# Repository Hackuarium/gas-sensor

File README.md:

# gas-sensor

The goal is to create a box allowing the determination of the gas composition of a bioreactor. The sensor that will be available are: CO2 (MH-Z19), H2 (MQ-8) and methane (MQ-4) as well as temperature (DS18B20) and humidity (DHT-22).

The board will be compatible with arduino Lilapad Pro using a dedicated PCB.

Need to compensate for humidity and temperature ???

- https://forum.arduino.cc/index.php?topic=433045.0

## Cloning the project

This project uses SUBMODULES

In order to clone use:

`git clone --recurse-submodules https://github.com/hackuarium/gas-sensor`

To update the submodules

`git submodule update --recursive --remote`

## Sensors

| name_pin | function    | model   |                             | Arduino library                                |
| -------- | ----------- | ------- | --------------------------- | ---------------------------------------------- |
| CH4      | CH4         | MQ-4    |                             |                                                |
| H2       | H2          | MQ-8    |                             |                                                |
| CO2      | CO2         | MH-Z19  | 3.3v (for RX / TX) + 5v!!!! | https://github.com/crisap94/MHZ19              |
| TEMP     | temperature | DS18B20 |                             |                                                |
| HUM      | humidity    | DHT-22  |                             | https://github.com/adafruit/DHT-sensor-library |

Gaz sensor: http://www.china-total.com/Product/meter/gas-sensor/Gas-sensor.htm

Gaz sensor on sparkfun:
https://www.sparkfun.com/products/8891
https://www.sparkfun.com/products/9404

Gaz sensor on mysensors: https://www.mysensors.org/build/gas

Drying the air / pumping
Particulate or Coalescing Filters
http://www.pneumaticplus.com/pneumaticplus-saf4000-series-particulate-air-filter-1-2-npt-with-bracket/
https://www.aliexpress.com/item/15L-M-12V-dc-electric-diaphragm-brush-small-air-compressor-pump/1790013118.html

Fans

https://www.pelonistechnologies.com/micro-fans

Pneumatic
https://www.alibaba.com/product-detail/A102-China-sup

## Pinout

| n° Arduino | port | pin      |                  |     |
| ---------- | ---- | -------- | ---------------- | --- |
| A0         | PC0  | A0       | H2               |     |
| A1         | PC1  | A1       | H2_ON            |     |
| A2         | PC2  | A2       | CO2_RX           |     |
| A3         | PC3  | A3       | CO2_TX           |     |
| A4         | PC4  | SDA      | Slave I2C        |     |
| A5         | PC5  | SCL      | Slave I2C        |     |
| A6         | ADC6 | A6       | CH4              |     |
| A7         | ADC7 | A7       | CH4_ON           |     |
| 0          | PD0  | RX       | FTDI             |     |
| 1          | PD1  | TX       | FTDI             |     |
| 2          | PD2  | D2       | /                |     |
| 3          | PD3  | D3       | PWM_MH-Z19       | PWM |
| 4          | PD4  | D4       | TEMPERATURE      |     |
| 5          | PD5  | D5       | HUMIDITY         | PWM |
| 6          | PD6  | D6       | LCD RS           | PWM |
| 7          | PD7  | D7       | /                |     |
| 8          | PB0  | D8       | LCD E            |     |
| 9          | PB1  | D9       | LCD LED          | PWM |
| 10         | PB2  | D10      | LCD1             | PWM |
| 11         | PB3  | MOSI D11 | LCD2             | PWM | mh |
| 12         | PB4  | MISO D12 | LCD3             |     |
| 13         | PB5  | SCK D13  | LCD4             |     |

n.b: Two pins (PD2 and PD7) are free and could be used to add a fourth sensor.

## Power supply

- plug for 5V
- MCP1703-33 for µC power supply

## Schematic
Here is the schematic of the main components of the project:

ATMega328P:

Sensors:

Others (LCD, crystal and voltage regulator):

## List of components
| Type           | Value | Quantity | Footprint                   |
|----------------|-------|----------|-----------------------------|
| Resistor       | 1M    | 1        | 0805 Handsolder             |
| Resistor       | 10k   | 2        | 0805 Handsolder             |
| Resistor       | 4.7k  | 2        | 0805 Handsolder             |
| Resistor       | 4.7   | 1        | 0805 Handsolder             |
| Potentiometer  |       | 1        | TRIM_3362R-1-222            |
| Capacitor      | 10µF  | 2        | 0805 Handsolder             |
| Capacitor      | 100nF | 3        | 0805 Handsolder             |
| Capacitor      | 18pF  | 2        | 0805 Handsolder             |
| Diode Shottky  |       | 3        | D_SOD-123                   |
| BSP75          |       | 2        | SOT-223-3_TabPin3           |
| Crystal        | 8Mhz  | 1        | Crystal_SMD_5032 Handsolder |
| MCP-1703A      |       | 1        | SOT-23                      |
| ATMega328P-AU  |       | 1        | TQFP-32_7x7mm_P0.8mm        |
| 5V power source|       | 1        | BarrelJack_Horizontal       |
| RJ12           |       | 1        | RJ12_Amphenol_54601         |
| LCD Screen     |       | 1        | WC1602A                     |
| MHZ-19 (CO2)   |       | 1        | footprints: MHZ-19          |
| MQ-4 (CH4)     |       | 1        | footprints: MQ-4            |
| MQ-8 (H2)      |       | 1        | footprints: MQ-8            |
| DHT22 (Hum)    |       | 1        | footprints: DHT-22_HOR      |
| DS18B20 (Temp) |       | 1        | TO-92_Inline                |

## Inspiration for PCB

* https://github.com/Hackuarium/esp-12e/tree/master/kicad

  - ICSP - TAG connect - take care of pin mapping !
  - RJ12 - 6P6C
  - FTDI232
  - LCD: WC1602A

## Get inspired from scale board

- https://github.com/Hackuarium/beemos/tree/master/scale-i2c/eagle
- https://github.com/Hackuarium/esp-12e/tree/master/kicad/libs

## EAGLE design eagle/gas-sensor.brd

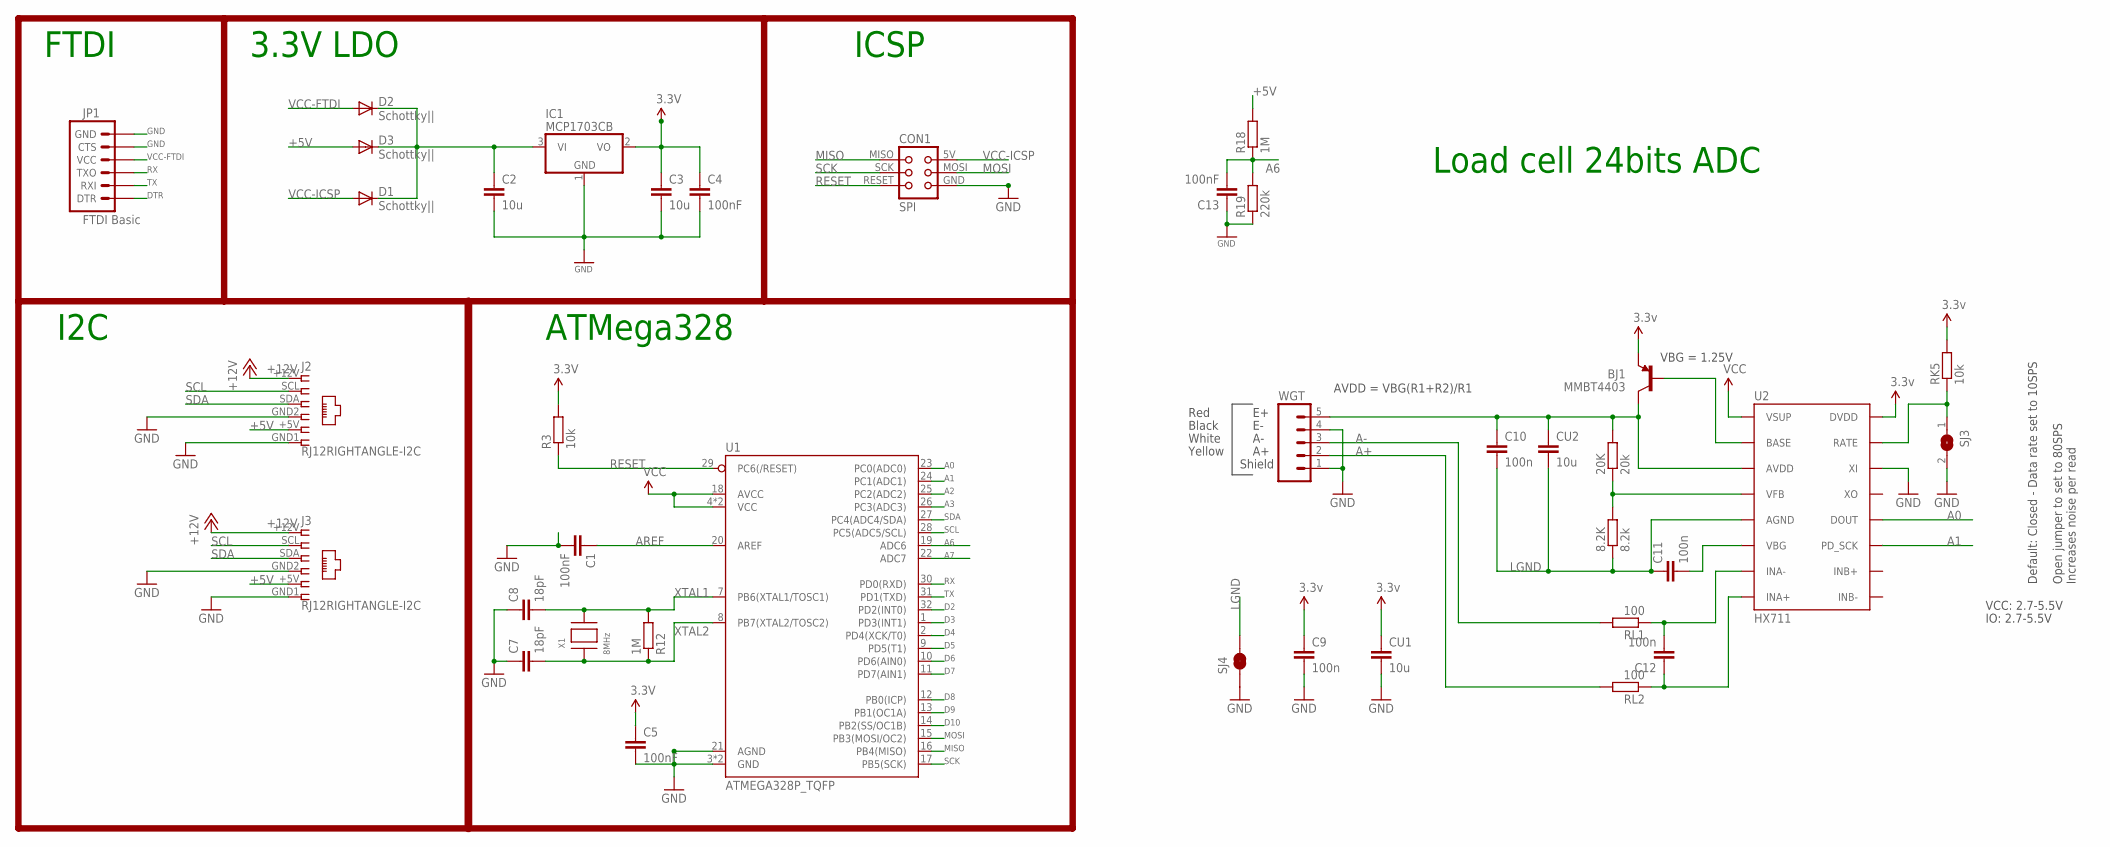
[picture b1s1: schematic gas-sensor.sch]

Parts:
8.2K: 8.2k; M0805
20K: 20k; M0805
BJ1: MMBT4403; SOT23-3
C1, C4, C5, C13: 100nF; C0805K; MPN 80-C1206C104K5R; LCSC C49678
C2, C3: 10u; C0805K; MPN 77-VJ1206V106ZXQTBC; LCSC C15850
C7, C8: 18pF; C0805K; MPN 77-VJ1206A180JXXPBC; LCSC C1797
C9, C10, C11, C12: 100n; C0805
CON1: SPI; TC2030-MCP
CU1, CU2: 10u; C0805
D1, D2, D3: Schottky||; SOD123; MPN 621-1N5819HW-F; LCSC C82544
IC1: MCP1703CB; SOT23; LCSC C53352
J2, J3: RJ12RIGHTANGLE-I2C; RJ12-RIGHTANGLE-I2C
JP1: FTDI Basic; 1X06
R3: 10k; R0805; LCSC C17513
R12, R18: 1M; R0805; LCSC C17514
R19: 220k; R0805; LCSC C17514
RK5: 10k; M0805
RL1, RL2: 100; M0805
SJ3: SJ
SJ4: JUMPER-PAD-2-NC_BY_TRACE; PAD-JUMPER-2-NC_BY_TRACE_YES_SILK
U1: ATMEGA328P_TQFP; TQFP32-08
U2: HX711; SO16
WGT: M05PTH; 1X05
X1: 8MHz; NX6035; MPN 729-F60800010; LCSC C122522

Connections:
3.3V: BJ1.2 (E), C3.1, C4.1, C5.1, C9.1, CU1.1, IC1.2 (VO), R3.2, RK5.2, U1.4 (VCC), U1.6 (VCC), U1.18 (AVCC), U2.1 (VSUP), U2.16 (DVDD)
+5V: D3.A, J2.+5V (5), J3.+5V (5), R18.2
+12V: J2.+12V (1), J3.+12V (1)
+XV: C2.1, D1.C, D2.C, D3.C, IC1.3 (VI)
A0: U1.23 (PC0(ADC0)), U2.12 (DOUT)
A1: U1.24 (PC1(ADC1)), U2.11 (PD_SCK)
A2: U1.25 (PC2(ADC2))
A3: U1.26 (PC3(ADC3))
A6: C13.2, R18.1, R19.2, U1.19 (ADC6)
A7: U1.22 (ADC7)
A+: RL2.2, WGT.2
A-: RL1.2, WGT.3
AREF: C1.1, U1.20 (AREF)
CN3: C11.2, U2.6 (VBG)
D2: U1.32 (PD2(INT0))
D3: U1.1 (PD3(INT1))
D4: U1.2 (PD4(XCK/T0))
D5: U1.9 (PD5(T1))
D6: U1.10 (PD6(AIN0))
D7: U1.11 (PD7(AIN1))
D8: U1.12 (PB0(ICP))
D9: U1.13 (PB1(OC1A))
D10: U1.14 (PB2(SS/OC1B))
DTR: JP1.1 (DTR)
GND: C1.2, C2.2, C3.2, C4.2, C5.2, C7.1, C8.1, C9.2, C13.1, CON1.GND, CU1.2, IC1.1 (GND), J2.GND1 (6), J2.GND2 (4), J3.GND1 (6), J3.GND2 (4), JP1.5 (CTS), JP1.6 (GND), R19.1, SJ3.2, SJ4.1, U1.3 (GND), U1.5 (GND), U1.21 (AGND), U2.14 (XI), WGT.1, WGT.4
LGND: 8.2K.1, C10.2, C11.1, CU2.2, SJ4.2, U2.5 (AGND)
MISO: CON1.MISO, U1.16 (PB4(MISO))
MOSI: CON1.MOSI, U1.15 (PB3(MOSI/OC2))
unnamed: 20K.2, BJ1.3 (C), C10.1, CU2.1, U2.3 (AVDD), WGT.5
unnamed: C12.2, RL1.1, U2.7 (INA-)
unnamed: BJ1.1 (B), U2.2 (BASE)
unnamed: 8.2K.2, 20K.1, U2.4 (VFB)
unnamed: RK5.1, SJ3.1, U2.15 (RATE)
unnamed: C12.1, RL2.1, U2.8 (INA+)
RESET: CON1.RESET, R3.1, U1.29 (PC6(/RESET))
RX: JP1.3 (TXO), U1.30 (PD0(RXD))
SCK: CON1.SCK, U1.17 (PB5(SCK))
SCL: J2.SCL (2), J3.SCL (2), U1.28 (PC5(ADC5/SCL))
SDA: J2.SDA (3), J3.SDA (3), U1.27 (PC4(ADC4/SDA))
TX: JP1.2 (RXI), U1.31 (PD1(TXD))
VCC-FTDI: D2.A, JP1.4 (VCC)
VCC-ICSP: CON1.5V (VCC), D1.A
XTAL1: C8.2, R12.2, U1.7 (PB6(XTAL1/TOSC1)), X1.P$2
XTAL2: C7.2, R12.1, U1.8 (PB7(XTAL2/TOSC2)), X1.P$1

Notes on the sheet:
ICSP
ATMega328
3.3V LDO
I2C
FTDI
VCC: 2.7-5.5V
VBG = 1.25V
AVDD = VBG(R1+R2)/R1
Default: Closed - Data rate set to 10SPS
Open jumper to set to 80SPS Increases noise per read
Red
Black
White
IO: 2.7-5.5V
Shield
Yellow
Load cell 24bits ADC

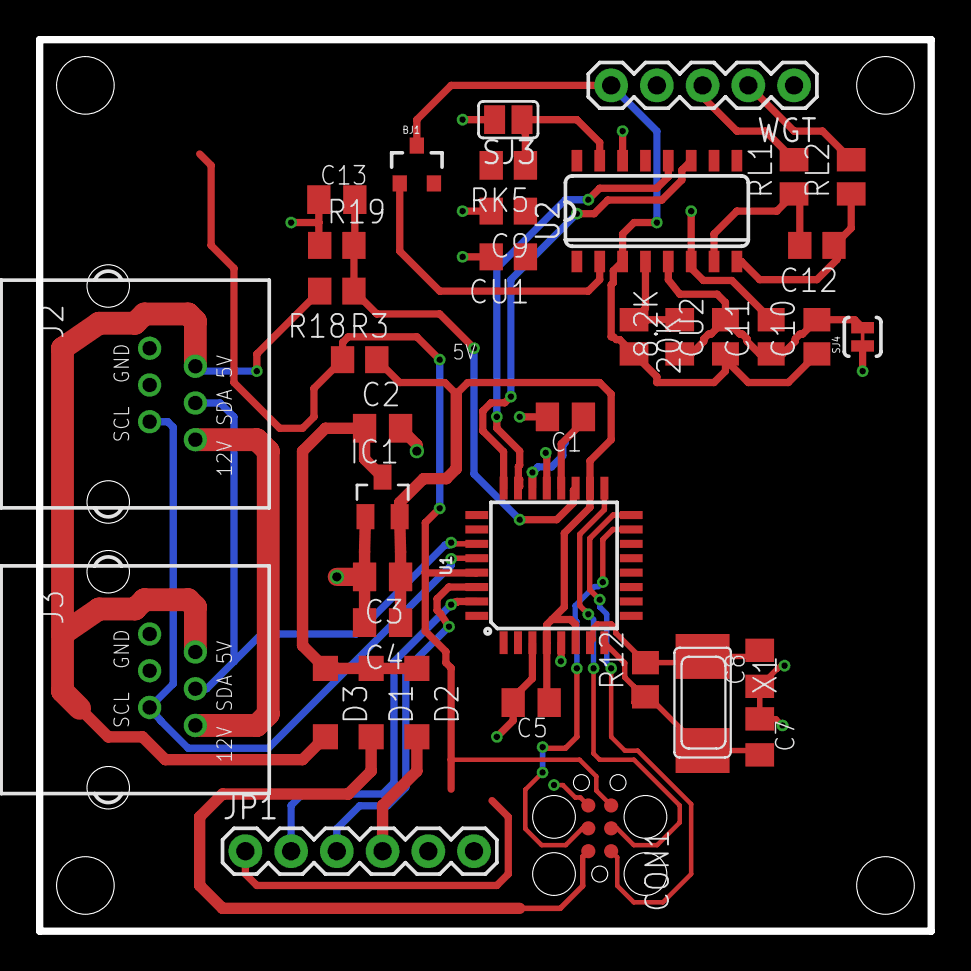
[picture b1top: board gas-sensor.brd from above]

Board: 2 copper layers, 49.5 x 49.5 mm, 38 parts (0 on the bottom side), 31 nets.

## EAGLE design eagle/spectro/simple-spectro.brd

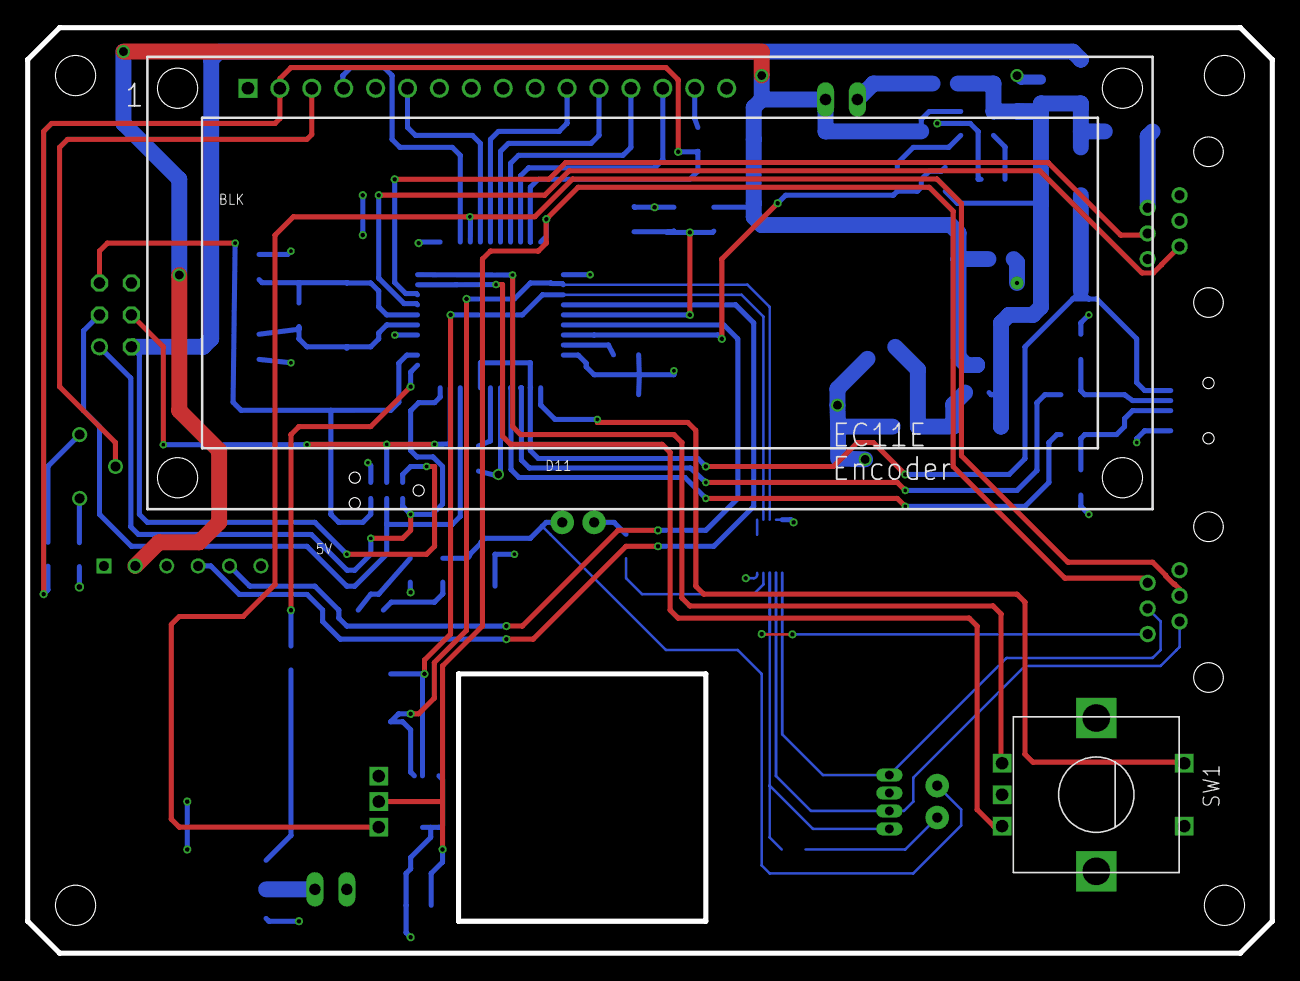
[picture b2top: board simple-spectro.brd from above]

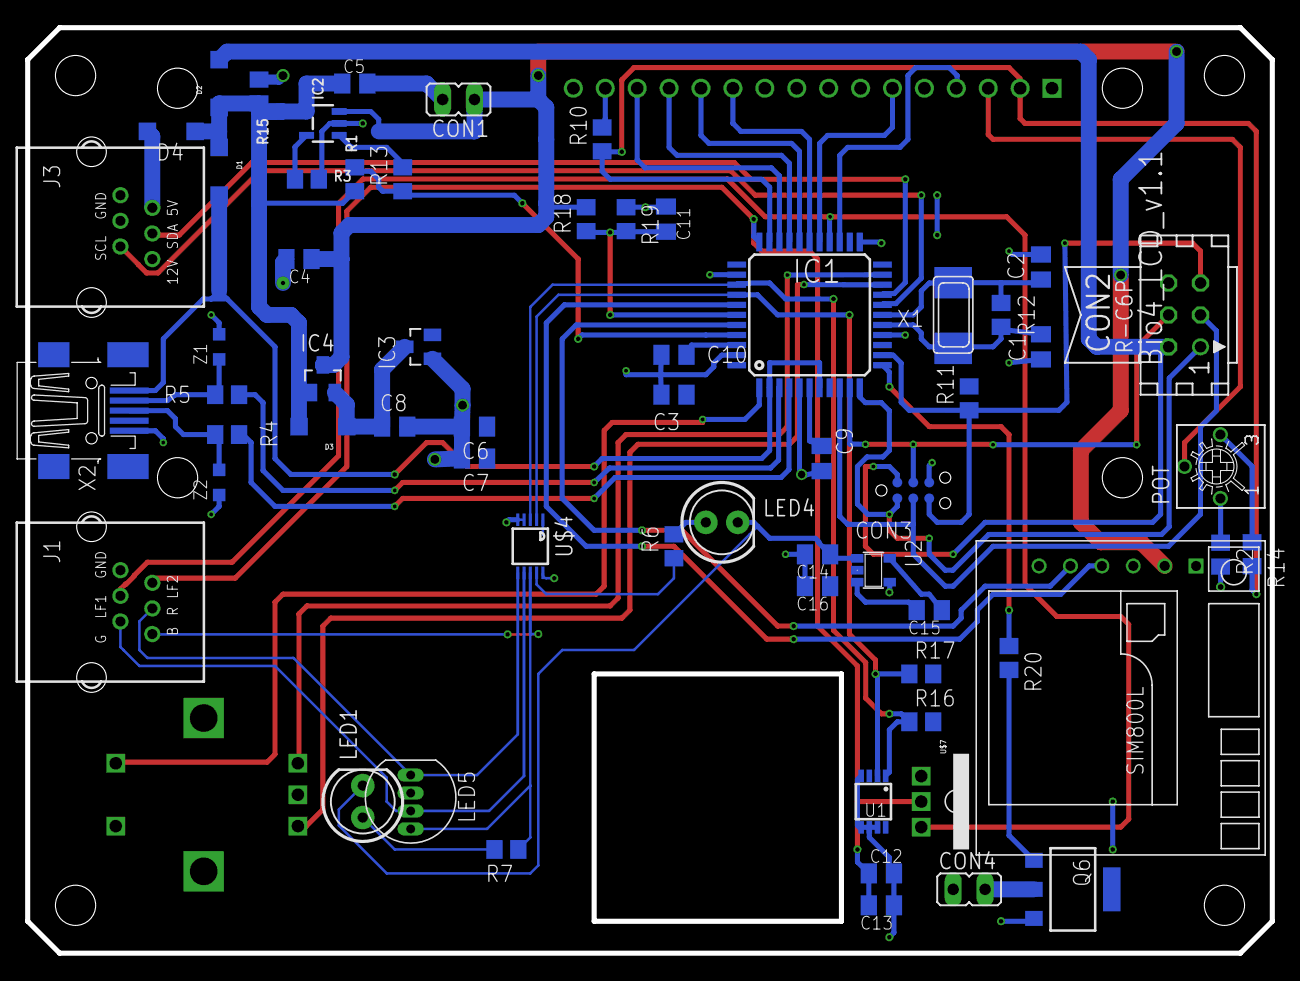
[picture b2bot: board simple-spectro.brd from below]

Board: 2 copper layers, 99.1 x 73.7 mm, 64 parts (62 on the bottom side), 58 nets.

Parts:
C1, C2: 18pF; C0805K
C3, C7, C9, C10, C11, C13: 100nF; C0805K
C4, C5, C6, C8, C12: 10u; C0805K
C14, C15, C16: 1u; C0805K
CON1: BAT; JP1
CON2: SPI; TINYISP
CON3: SPI; TC2030-MCP-NL
CON4: VIBR; JP1
D1, D2, D3, D4: Schottky; SOD123
IC1: 32U4; TQFP44
IC2: MCP73831T; SOT23-5
IC3: MCP1703-33-CB; SOT23
IC4: DMP1045U; SOT-23
J1: RJ12RIGHTANGLE-BIO; RJ12-RIGHTRANGE-RGB
J3: RJ12RIGHTANGLE-I2C; RJ12-RIGHTANGLE-I2C
LCD: LCD-HD447804-HOLES16X2-4-HOLES; LCD-16X2-4HOLES
LED1, LED4: UV; LED5MM
LED5: RGB-COMMON-CATHODE; LED-TRICOLOR-THROUGHHOLE
POT: 10k; TRIMMER_3362P
Q6: BSP75; PG-SOT-223
R1, R3, R13, R16, R17: 10k; R0805
R2, R6, R7, R14: 100; R0805
R4, R5: 22; R0805
R10: 0; R0805
R11, R15: 100k; R0805
R12, R18, R19: 1M; R0805
R20: 1k; R0805
SW1: EC12E_SW; ALPS_EC12E_SW
U1: NCT75DMR2G; MSOP8
U2: TPS60400DVBR; SOT23-5
U$1: SIM800LMODULE
U$4: MCP4728; MSOP10
U$7: TSL237
X1: 8MHz; NX6035
X2: MINI-USB; 32005-201
Z1, Z2: VARISTOR; CT/CN0603

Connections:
-VCC: C14.1, LED1.K, LED4.K, U2.1
A0: IC1.36, R16.1, U1.1, U$4.3
A1: IC1.37, R17.1, U1.2, U$4.2
A2: IC1.38, U$1.RX
A3: C11.2, IC1.39, R18.1, R19.2
A4: IC1.40, U$1.TX
A5: IC1.41, R1.2, R13.1
A6: IC1.25, LCD.4
AREF: C10.1, IC1.42
D5: IC1.31, LCD.14
D6: IC1.27, LCD.6
D7: IC1.1, SW1.D
D8: IC1.28, LCD.11
D9: IC1.29, LCD.12
D10: IC1.30, LCD.13
D11: IC1.12, R20.1
D12: IC1.26, J1.LF1, U$7.OUT
D13: IC1.32, LCD.2, R10.1, R14.2
GND: C1.1, C2.1, C3.1, C4.2, C5.2, C6.2, C7.2, C8.2, C9.1, C10.2, C11.1, C12.2, C13.1, C14.2, C16.2, CON1.2, CON2.GND, CON3.GND, IC1.5, IC1.15, IC1.23, IC1.35, IC1.43, IC2.2, IC3.1, J1.GND, J3.GND1, J3.GND2, LCD.1, LCD.5, LCD.16, LED5.GND, Q6.3, R2.2, R3.2, R15.1, R19.1, SW1.C, SW1.E, U1.4, U1.5, U1.6, U1.7, U2.4, U$1.GND, U$4.4, U$4.5, U$4.10, U$7.GND, X2.5, Z1.2, Z2.1
HWB: C12.1, C13.2, IC1.33, J1.LF2, U$7.VDD
ISP+5V: CON2.VCC, CON3.5V, D2.A
L1: J1.G, LED5.GRN, U$4.7
L2: J1.R, LED5.RED, U$4.6
L3: J1.B, LED5.BLU, R7.1, U$4.8
L4: R6.1, U$4.9
MISO: CON2.MISO, CON3.MISO, IC1.11
MOSI: CON2.MOSI, CON3.MOSI, IC1.10
unnamed: C9.2, IC1.6
unnamed: LCD.3, POT.2
unnamed: D4.A, J3.+5V
unnamed: POT.1, R2.1
unnamed: IC2.1, R13.2
unnamed: IC2.5, R3.1
unnamed: LED4.A, R6.2
unnamed: Q6.1, R20.2
unnamed: LED1.A, R7.2
unnamed: LCD.15, R10.2
unnamed: POT.3, R14.1
unnamed: CON4.2, Q6.2
unnamed: C5.1, D1.C, D2.C, D3.A, D4.C, IC2.4, IC4.1, R1.1, R15.2
unnamed: C15.2, U2.3
unnamed: C15.1, U2.5
unnamed: C2.2, IC1.17, R12.2, X1.P$2
RESET: CON2.RESET, CON3.RESET, IC1.13, R11.1
RX: IC1.20, SW1.B
SCK: CON2.SCK, CON3.SCK, IC1.9
SCL: IC1.18, J3.SCL
SDA: IC1.19, J3.SDA
TX: IC1.21, SW1.A
USBC_N: R5.2, X2.2, Z1.1
USBC_P: R4.2, X2.3, Z2.2
USB_N: IC1.3, R5.1
USB_P: IC1.4, R4.1
VBAT1: C4.1, CON1.1, IC2.3, IC4.3, R18.2, U$1.VCC
VCC: C3.2, C6.1, C7.1, C16.1, CON4.1, IC1.14, IC1.24, IC1.34, IC1.44, IC3.2, R11.2, R16.2, R17.2, U1.8, U2.2, U$1.RST, U$4.1
VDD: C8.1, D3.C, IC3.3, IC4.2
VUSB: D1.A, IC1.2, IC1.7, X2.1
XTAL1: C1.2, IC1.16, R12.1, X1.P$1

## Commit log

2018-12-04 add specdtro
2019-02-05 description of new project
2019-02-05 add pwm information
2019-02-05 update CO2 gas sensor and reset
2019-02-05 add link to gas sensor
2019-02-05 add remarks about temperature
2019-02-13 Add Olivier file
    First draft of shematic
2019-02-21 add more info in readme
2019-02-26 Footprints and first PCB draft
    add kicad (+libs) and docs file, sorted libs, footprints of sensors, first draft of PCB
2019-02-26 minor changes
2019-03-05 First version of PCB
    with 3D components
2019-03-07 Update README.md
    change PIN configuration
2019-03-13 Update
    With space for plexiglas box
2019-03-14 add gerber files and version
2019-03-14 update pcb and submit gerber
2019-03-22 Update after debugging
2019-03-25 gerver v1.1.0
2019-03-26 add missing dri files in gerber.110
2019-04-01 add first multithread program
2019-04-02 improve code
2019-04-08 Rx/Tx + Potentiometer ok
2019-04-10 Update
    Plans for laser cut (simple & with clips)
2019-04-10 Delete eagle file
    Unused and useless
2019-04-10 Added voltage regulator
2019-04-22 Update CAD
2019-04-30 Update PCB
    ready for GERBER
2019-05-17 Final version of box
2019-05-17 Add images schématic
2019-05-24 Update Code

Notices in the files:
parts and their libraries:
lpatiny: ©2009 ROFA.cz - modified and updated by Robert Darlington ‹rdarlington@gmail.com›
SparkFun-IC-Microcontroller: Licensing: Creative Commons ShareAlike 4.0 International - https://creativecommons.org/licenses/by-sa/4.0
